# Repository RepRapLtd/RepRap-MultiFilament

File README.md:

# RepRap-MultiFilament
Multi filament drive for RepRap and other FFF printers

The drive has three components:

  1. Multi-drive - a pinch-wheel drive for multiple filaments driven by a single stepper and a small DC motor.
  2. Guillotine - a device that cuts filament driven by the same small DC motor.
  3. Filament-Y - a passive device that merges feeds of filament into a single Bowden channel.

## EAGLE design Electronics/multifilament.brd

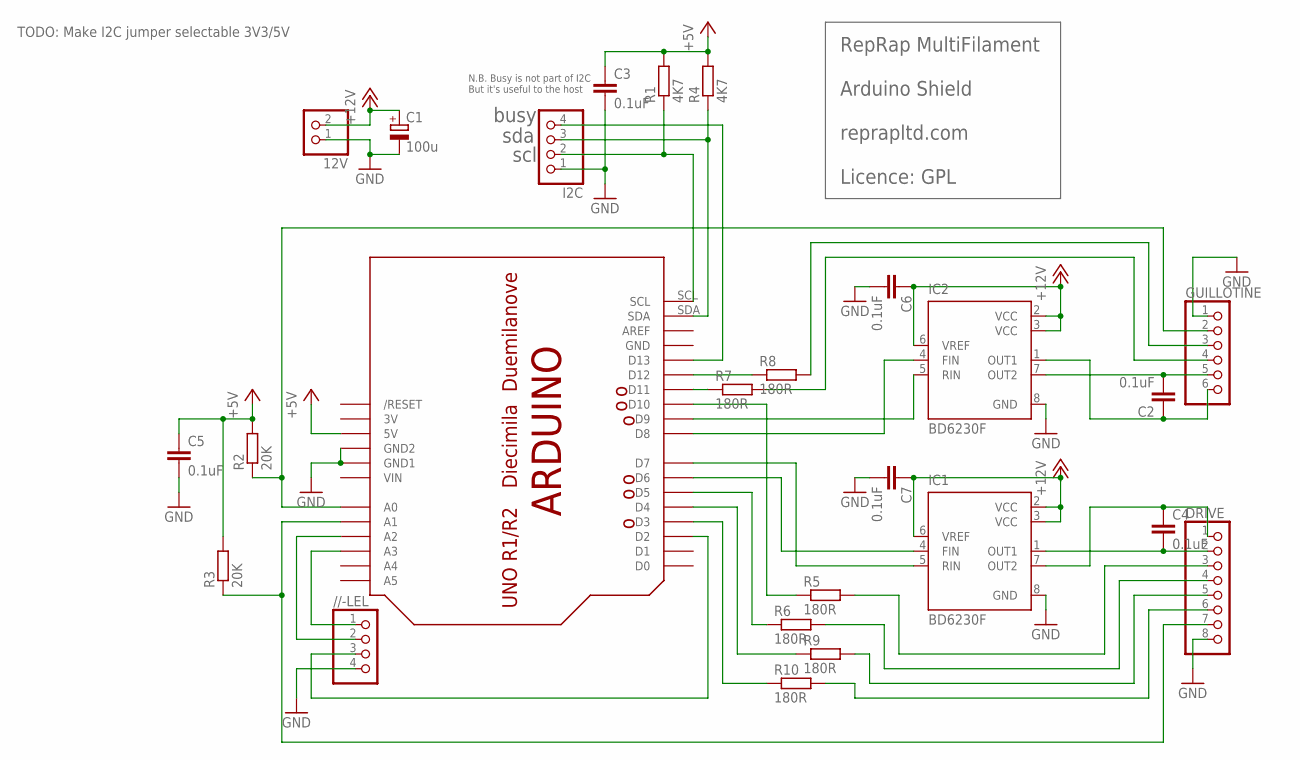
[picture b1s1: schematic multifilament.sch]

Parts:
12V: PINHD-1X2; 1X02
//-LEL: PINHD-1X4; 1X04
C1: 100u; SANYO-OSCON_9F
C2, C3, C4, C5, C6, C7: 0.1uF; C0805
DRIVE: PINHD-1X8; 1X08
GUILLOTINE: PINHD-1X6; 1X06
I2C: PINHD-1X4; 1X04
IC1, IC2: BD6230F; SOP8
R1, R4: 4K7; M0805
R2, R3: 20K; M0805
R5, R6, R7, R8, R9, R10: 180R; M0805
U$1: ARDUINO-BPLACE

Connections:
3V: U$1.3V
+5V: C3.1, C5.1, R1.2, R2.2, R3.2, R4.2, U$1.5V
+12V: 12V.2, C1.+, C6.1, C7.1, IC1.2 (VCC), IC1.3 (VCC), IC1.6 (VREF), IC2.2 (VCC), IC2.3 (VCC), IC2.6 (VREF)
GND: 12V.1, //-LEL.4, C1.-, C3.2, C5.2, C6.2, C7.2, DRIVE.8, GUILLOTINE.1, I2C.1, IC1.8 (GND), IC2.8 (GND), U$1.GND, U$1.GND1, U$1.GND2
unnamed: I2C.2, R1.1, U$1.SCL
unnamed: GUILLOTINE.2, R2.1, U$1.A0
unnamed: C2.2, GUILLOTINE.5, IC2.7 (OUT2)
unnamed: C4.2, DRIVE.2, IC1.1 (OUT1)
unnamed: R6.1, U$1.D5
unnamed: IC1.4 (FIN), U$1.D6
unnamed: IC1.5 (RIN), U$1.D7
unnamed: IC2.4 (FIN), U$1.D8
unnamed: I2C.3, R4.1, U$1.SDA
unnamed: DRIVE.7, R3.1, U$1.A1
unnamed: IC2.5 (RIN), U$1.D9
unnamed: I2C.4, U$1.D13
unnamed: GUILLOTINE.3, R8.2
unnamed: R7.1, U$1.D11
unnamed: GUILLOTINE.4, R7.2
unnamed: R8.1, U$1.D12
unnamed: R5.1, U$1.D10
unnamed: DRIVE.3, R5.2
unnamed: DRIVE.4, R6.2
unnamed: R9.1, U$1.D4
unnamed: DRIVE.5, R9.2
unnamed: R10.1, U$1.D3
unnamed: DRIVE.6, R10.2
unnamed: //-LEL.2, U$1.A2
unnamed: //-LEL.1, U$1.A3
unnamed: //-LEL.3, U$1.D2
unnamed: C4.1, DRIVE.1, IC1.7 (OUT2)
unnamed: C2.1, GUILLOTINE.6, IC2.1 (OUT1)
VIN: U$1.VIN

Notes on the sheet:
RepRap MultiFilament Arduino Shield reprapltd.com Licence: GPL
busy
sda
scl
N.B. Busy is not part of I2C But it's useful to the host
TODO: Make I2C jumper selectable 3V3/5V

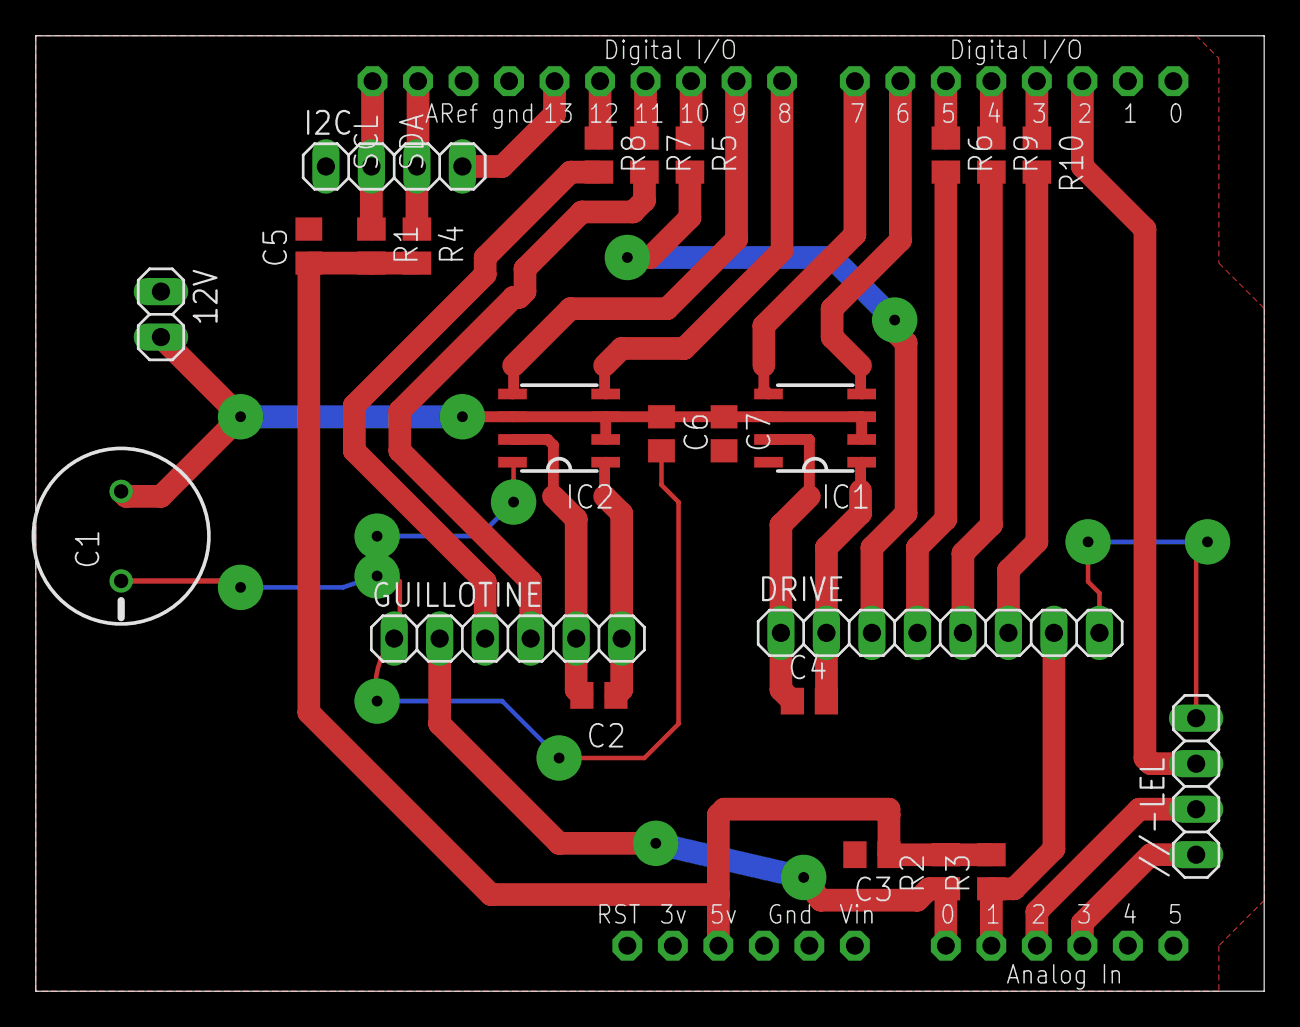
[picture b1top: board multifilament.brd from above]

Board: 2 copper layers, 68.6 x 53.3 mm, 25 parts (0 on the bottom side), 31 nets.

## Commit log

2019-01-16 First commit.
2019-01-16 File reorganising.
2019-01-18 New guillotine. WIP.
2019-01-21 New guillotine design fininshed?
2019-01-24 Improved design of guillotine arm.
2019-01-29 Guillotine with photosensors added.
2019-01-31 Guillotine sensor wiring finished (?).
2019-02-06 First design of Arduino Uno shield electronics.
2019-02-08 First working version of guillotine software.
2019-02-11 Tuning up the light detection.
2019-02-12 Parameters adjusted in software - first working version.
2019-02-22 Improving the multi-drive design. Making the clamp wheel adjustable.
2019-03-01 Improved filament clamp design. All GCode folders gone.
2019-11-28 Making Prusa MMU2 etc a submodule
2019-11-28 Added i3 as a submodule
